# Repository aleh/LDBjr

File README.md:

# LDBjr

Simple analogue drum machine with kick, snare, and hi-hat.

This is based [this schematics from Delptronics](http://mickeydelp.com/blog/anatomy-of-a-drum-machine) but is missing many drums and the hardware sequencer. 

See [MIDIMonkey](https://github.com/aleh/MIDIMonkey) for a simple MIDI trigger and [NoiseChip](https://github.com/aleh/NoiseChip) for the "noise" chip referenced in the schematics.

Note that the PCB layout is not good, I was using it only to guide my assembly on protoboards.

---

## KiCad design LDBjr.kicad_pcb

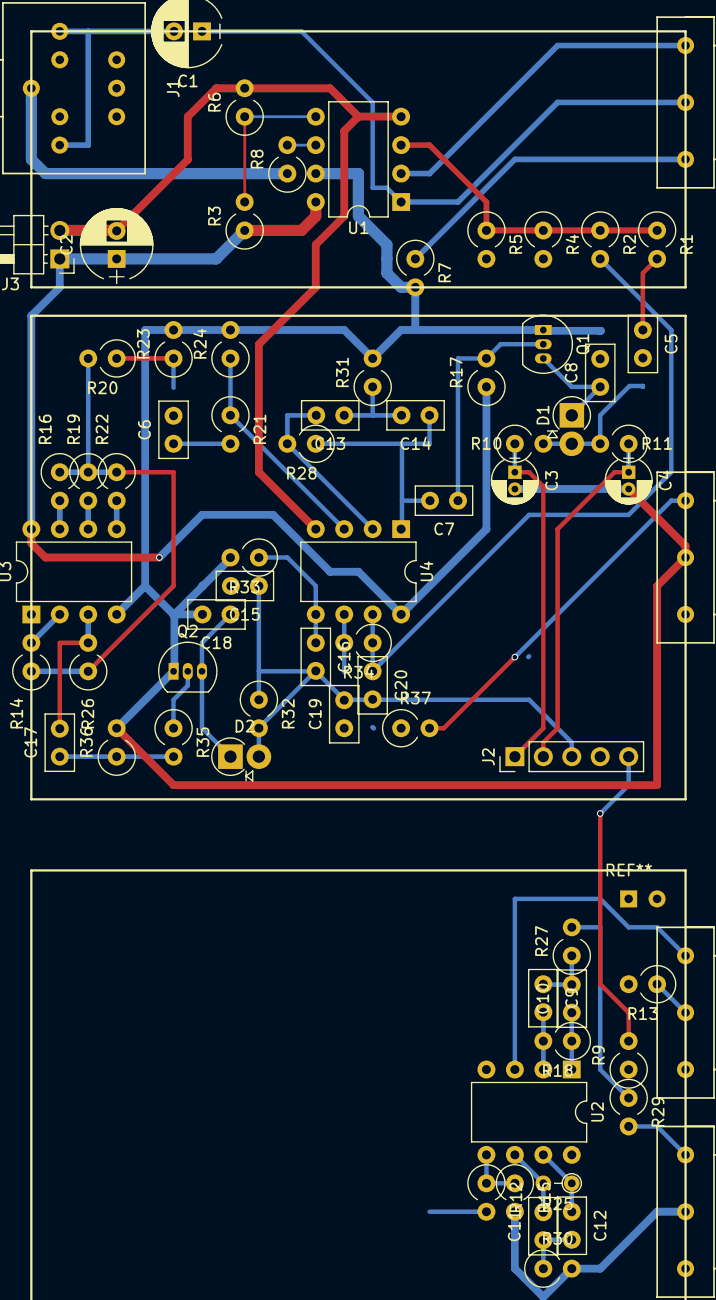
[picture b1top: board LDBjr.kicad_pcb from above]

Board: 2 copper layers, 72 parts (0 on the bottom side), 52 nets.

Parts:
C1, C2: 220u; CP_Radial_D6.3mm_P2.50mm
C3: 1u; CP_Radial_D4.0mm_P1.50mm
C4: 2u2; CP_Radial_D4.0mm_P1.50mm
C5: 100n; C_Disc_D5.0mm_W2.5mm_P2.50mm
C6: 1n; C_Disc_D5.0mm_W2.5mm_P2.50mm
C7: 47n; C_Disc_D5.0mm_W2.5mm_P2.50mm
C8, C18: 470p; C_Disc_D5.0mm_W2.5mm_P2.50mm
C9, C10: 68n; C_Disc_D5.0mm_W2.5mm_P2.50mm
C11, C12: 6n8; C_Disc_D5.0mm_W2.5mm_P2.50mm
C13, C14: 3.3n; C_Disc_D5.0mm_W2.5mm_P2.50mm
C15: 330n; C_Disc_D5.0mm_W2.5mm_P2.50mm
C16: C; C_Disc_D5.0mm_W2.5mm_P2.50mm
C17: 68p; C_Disc_D5.0mm_W2.5mm_P2.50mm
C19, C20: 33n; C_Disc_D5.0mm_W2.5mm_P2.50mm
D1, D2: D; D_DO-41_SOD81_P2.54mm_Vertical_AnodeUp
J1: PHONES; JACK_3
J2: MIDIMonkey; Pin_Header_Straight_1x05_Pitch2.54mm
J3: POWER; Pin_Header_Angled_1x02_Pitch2.54mm
Q1, Q2: 2N3904; TO-92_Inline_Narrow_Oval
R1: 6K8; R_Axial_DIN0309_L9.0mm_D3.2mm_P2.54mm_Vertical
R2, R5, R9, R23, R24: 10K; R_Axial_DIN0309_L9.0mm_D3.2mm_P2.54mm_Vertical
R3, R6: 5K1; R_Axial_DIN0309_L9.0mm_D3.2mm_P2.54mm_Vertical
R4: 20K; R_Axial_DIN0309_L9.0mm_D3.2mm_P2.54mm_Vertical
R7: 5K; R_Axial_DIN0309_L9.0mm_D3.2mm_P2.54mm_Vertical
R8, R15, R27, R30, R33: 1K; R_Axial_DIN0309_L9.0mm_D3.2mm_P2.54mm_Vertical
R10, R11, R12: 47K; R_Axial_DIN0309_L9.0mm_D3.2mm_P2.54mm_Vertical
R13: 200; R_Axial_DIN0309_L9.0mm_D3.2mm_P2.54mm_Vertical
R14, R16, R19, R22, R32: 100K; R_Axial_DIN0309_L9.0mm_D3.2mm_P2.54mm_Vertical
R17, R18, R20, R26, R34, R35, R36: 1M; R_Axial_DIN0309_L9.0mm_D3.2mm_P2.54mm_Vertical
R21: 22K; R_Axial_DIN0309_L9.0mm_D3.2mm_P2.54mm_Vertical
R25: 2M; R_Axial_DIN0204_L3.6mm_D1.6mm_P2.54mm_Vertical
R28: 82K; R_Axial_DIN0309_L9.0mm_D3.2mm_P2.54mm_Vertical
R29, R37: 330; R_Axial_DIN0309_L9.0mm_D3.2mm_P2.54mm_Vertical
R31: 560; R_Axial_DIN0309_L9.0mm_D3.2mm_P2.54mm_Vertical
RV1, RV2: 10K; POT
RV3, RV4: 1K; POT
U1: NE5532; DIP-8_W7.62mm
U2, U4: TL072; DIP-8_W7.62mm
U3: ATtiny85; DIP-8_W7.62mm

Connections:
+BATT: C2.1, J3.1, R3.1, R17.1, U1.8, U2.8, U3.8, U4.8
-BATT: C2.2, J3.2, R6.2, U1.4, U2.4, U4.4
BD: J2.5, R9.2
BD_MIX: C10.1, R4.2, R18.1, U2.1
CH: C3.1, J2.1, R10.1
GND: C3.2, C4.2, C8.2, C15.2, C18.2, J1.3, Q1.1, Q2.1, R7.2, R8.1, R13.2, R15.2, R23.2, R24.2, R30.2, R31.2, R33.2, R36.2, RV3.3, RV4.3, U1.7, U3.4
HAT_MIX: C5.1, R1.2
HT: J2.4, R12.2
HT_MIX: C12.1, R5.2, R25.1, U2.7
unnamed: C1.1, RV1.3, U1.1
unnamed: C1.2, J1.1, J1.2
unnamed: C5.2, D1.2, R10.2, R11.2
unnamed: C6.1, R21.2
unnamed: C6.2, R20.1, R23.1
unnamed: C7.1, Q1.2, R17.2
unnamed: C8.1, D1.1, Q1.3
unnamed: C9.2, R18.2, U2.2
unnamed: C9.1, C10.2, R27.1
unnamed: C11.1, C12.2, R30.1
unnamed: C11.2, R25.2, U2.6
unnamed: C13.1, C14.2, R31.1
unnamed: C13.2, R28.2, U4.2
unnamed: C7.2, C14.1, R28.1, U4.1
unnamed: C16.1, R33.1, U4.5
unnamed: C16.2, D2.2, R32.2
unnamed: C17.1, R35.2, R36.1
unnamed: C17.2, R26.2, U3.3
unnamed: C18.1, D2.1, Q2.3
unnamed: C19.1, C20.2, R37.1
unnamed: C19.2, R34.2, U4.6
unnamed: Q2.2, R35.1
unnamed: R1.1, R2.1, R4.1, R5.1, U1.3
unnamed: R3.2, R6.1, U1.5
unnamed: R7.1, RV1.1
unnamed: R8.2, U1.6
unnamed: R9.1, RV2.1
unnamed: R12.1, R15.1, U2.5
unnamed: R13.1, RV2.3
unnamed: R14.1, R16.1, R19.1, R20.2, R22.1, R26.1
unnamed: R14.2, U3.2
unnamed: R16.2, U3.7
unnamed: R19.2, U3.6
unnamed: R21.1, R24.1, U4.3
unnamed: R22.2, U3.5
unnamed: R27.2, R29.1
unnamed: R29.2, RV3.2
unnamed: R37.2, RV4.2
unnamed: RV1.2, U1.2
unnamed: RV2.2, U2.3
OH: C4.1, J2.2, R11.1
SD: C15.1, J2.3, R32.1
SD_MIX: C20.1, R2.2, R34.1, U4.7

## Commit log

2018-05-01 Add basic README
2018-05-01 Fixup the subproject links
2018-05-01 Got rid of the kicad project file
